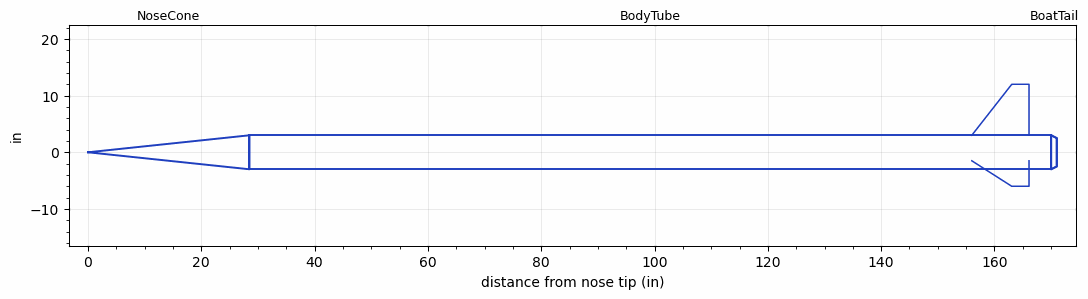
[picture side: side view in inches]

<RASAeroDocument>
 <FileVersion>2</FileVersion>
 <RocketDesign>
  <NoseCone>
   <Length>28.5</Length>
   <Diameter>6</Diameter>
   <Shape>Conical</Shape>
   <BluntRadius>0.25</BluntRadius>
   <Location>0</Location>
  </NoseCone>
  <BodyTube>
   <Length>141.5</Length>
   <Diameter>6</Diameter>
   <RailGuideDiameter>1.5</RailGuideDiameter>
   <RailGuideHeight>0.7</RailGuideHeight>
   <Location>28.5</Location>
   <BoattailLength>1</BoattailLength>
   <BoattailRearDiameter>5</BoattailRearDiameter>
   <Fin>
    <Count>3</Count>
    <Chord>10.1</Chord>
    <Span>9</Span>
    <SweepDistance>7.05</SweepDistance>
    <TipChord>3.05</TipChord>
    <Thickness>0.1875</Thickness>
    <Location>14</Location>
    <AirfoilSection>Hexagonal</AirfoilSection>
    <FX1>2</FX1>
    <FX3>1</FX3>
   </Fin>
  </BodyTube>
  <BoatTail>
   <Length>1</Length>
   <Diameter>6</Diameter>
   <RearDiameter>5</RearDiameter>
   <Location>170</Location>
  </BoatTail>
  <Surface>Smooth (Zero Roughness)</Surface>
  <ModifiedBarrowman>False</ModifiedBarrowman>
  <Turbulence>False</Turbulence>
  <SustainerNozzle>4.8</SustainerNozzle>
  <UseBooster1>False</UseBooster1>
  <UseBooster2>False</UseBooster2>
  <Comments>Proteus 6
Loki Research P9381 Solid Rocket Motor
Curt Newport and Jeff Taylor

Carried 2 ARTS Instrumentation Packages - Accelerometer, Barometric Altimeter, and GPS.

Apogee Altitude 85067 ft based on integrated accelerometer data, average of the two accelerometers.
RASAero II Prediction = 81499 ft, Error = -4.19%

Maximum Velocity 3201 ft/sec (Mach 2.94) based on integrated accelerometer data, average of the two accelerometers.
RASAero II Prediction = 3063 ft/sec, Error = -4.31%

Barometric Altimeter data and GPS data during parachute descent from 46000 ft to landing.  Parachute descent time apogee to landing = 529 sec.
RASAero II Prediction = 480 sec, Error = -9.26%
</Comments>
 </RocketDesign>
 <LaunchSite>
  <Altitude>3933</Altitude>
  <Pressure>0</Pressure>
  <RodAngle>2</RodAngle>
  <RodLength>18</RodLength>
  <Temperature>80</Temperature>
  <WindSpeed>0</WindSpeed>
 </LaunchSite>
 <Recovery>
  <Altitude1>1000</Altitude1>
  <Altitude2>1000</Altitude2>
  <DeviceType1>Parachute</DeviceType1>
  <DeviceType2>None</DeviceType2>
  <Event1>True</Event1>
  <Event2>False</Event2>
  <Size1>45.5</Size1>
  <Size2>1</Size2>
  <EventType1>Apogee</EventType1>
  <EventType2>None</EventType2>
  <CD1>1.33</CD1>
  <CD2>1.33</CD2>
 </Recovery>
 <SimulationList>
  <Simulation>
   <SustainerEngine>P9381  (LR-EX)</SustainerEngine>
   <SustainerLaunchWt>186.7</SustainerLaunchWt>
   <SustainerNozzleDiameter>4.8</SustainerNozzleDiameter>
   <SustainerCG>111</SustainerCG>
   <SustainerIgnitionDelay>0</SustainerIgnitionDelay>
   <Booster1SeparationDelay>0</Booster1SeparationDelay>
   <Booster1IgnitionDelay>0</Booster1IgnitionDelay>
   <IncludeBooster1>False</IncludeBooster1>
   <Booster2Delay>0</Booster2Delay>
   <IncludeBooster2>False</IncludeBooster2>
   <TimetoApogee>68.73627</TimetoApogee>
   <MaxAltitude>81498.75</MaxAltitude>
   <MaxVelocity>3062.629</MaxVelocity>
  </Simulation>
 </SimulationList>
</RASAeroDocument>
